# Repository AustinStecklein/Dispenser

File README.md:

# Dispenser
Creedmoor code base for the powder dispenser

# TODO List Software
- [ ] forward and back buttons dont function
- [ ] brightness/sound page sliders need to be prettier if possible
- [ ] calibrate, default settings, power off need yes and no image buttons
- [ ] Force the Subpages of Settings to not appear after clicking on the home button   and then clicking on Settings
- [ ] Keyboard does the same thing as the Settings subpages
- [ ] Replace the Boot Logo when the Program starts with a Creedmoor Logo

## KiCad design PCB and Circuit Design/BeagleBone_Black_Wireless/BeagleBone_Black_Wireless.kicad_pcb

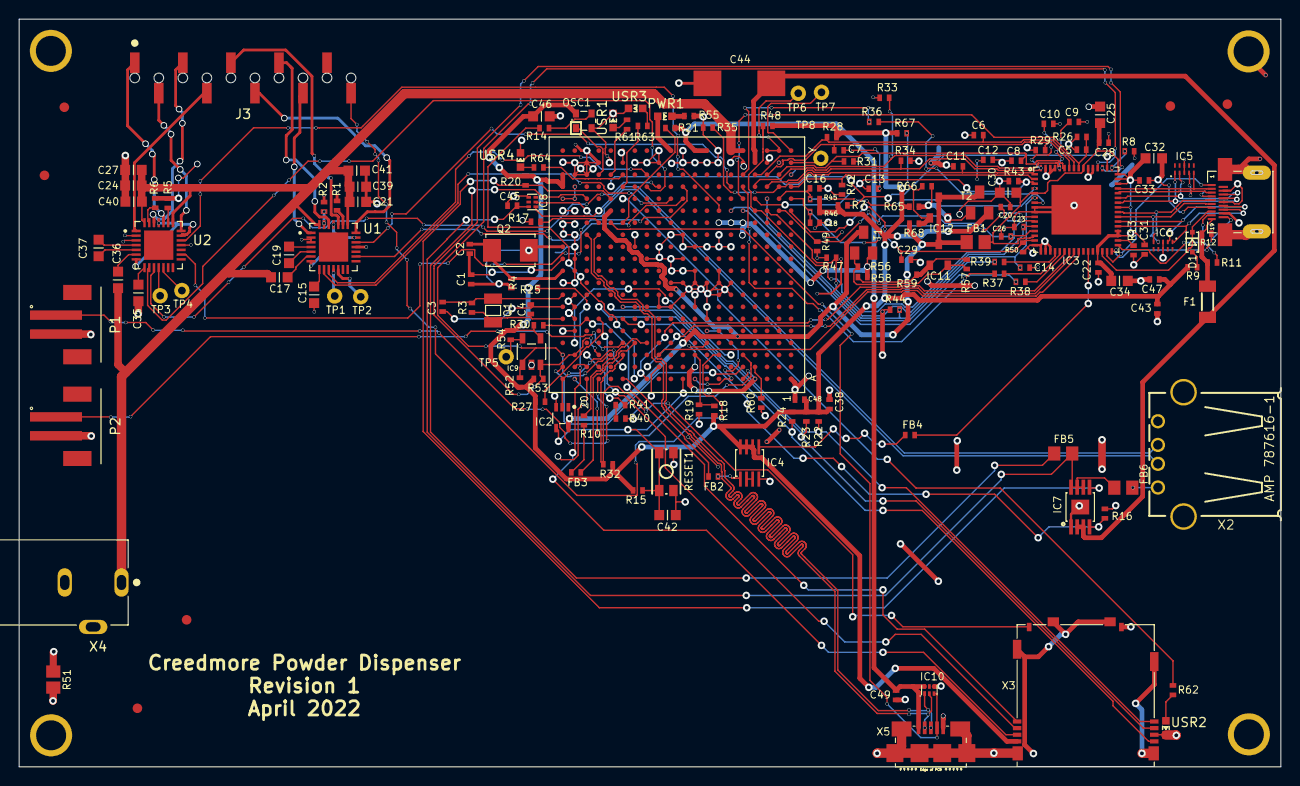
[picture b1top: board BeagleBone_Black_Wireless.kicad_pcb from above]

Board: 2 copper layers, 133.4 x 79.0 mm, 176 parts (0 on the bottom side), 159 nets.

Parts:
C1, C2, C3, C4: 18pF, 50V; C0402K
C5, C6, C7, C8, C9, C10, C11, C12, C13, C14, C16, C18, C20, C23, C26, C29: 47pF, 6.3V; C0402K
C15, C35: 10uF; C0603K
C17, C21, C24, C36, C39, C40: 100nF; C0603K
C19, C37: 22nF; C0603K
C22, C28, C31, C33, C38, C43, C45, C47, C48, C49: .1uF, 6.3V; C0402K
C25, C30, C32, C34, C42: 2.2uF, 6.3V; C0603K
C27, C41: 100uF; C0603K
C44: 220uF 6.3V; D_7343-31W
C46: 10uF,10V; C0603K
D1: RB751V40,115; SOD323(NXP)REFLOW
F1: 1206L025YR; SM-1206
FB1: 2.5k Ohm (BLM18BD252SN1D); 0805-RESISTOR
FB2, FB3, FB4: 1k BLM15AG102SN1D; R0402
FB5: 0.1 Ohm, 0805; 0805-RESISTOR
FB6: 150 Ohm 800mA; 0805-RESISTOR
FUD1, FUD2, FUD3, FUD4, FUD5, FUD6: FIDUCIAL; FIDUCIAL_40MIL
IC1: OSD3358
IC2: SN74LVC1G07DCK; SC70(TI-DCK)
IC3: TDA19988BHN/C1,557; SOT804-4(NXP)
IC4: SN74AUC1G74; SM8-8(TI)
IC5, IC6: IP4283CZ10-TBR; SOT1176-1(NXP)
IC7: TPS2051BDGN; MSOP-POWER.PAD-8(TI)
IC8, IC10: TPD4S012DRY; SON-6(TI)-DRY
IC9: 24LC32AT-I/OT; SOT23-5(MICROCHIP)
IC11: TLVH431 (SOT-23-3); DBZ_R-PDSO-G3
IC12: DNP TLVH431 (SOT-23-3); DBZ_R-PDSO-G3
J3: BG125-10-A-1-1-0440-N-D; GCT_BG125-10-A-1-1-0440-N-D
MGT1, MGT2, MGT3, MGT4: MOUNTING_HOLE
OSC1: ASDMB-24.576MHZ-LC-T; OSCILLATOR-2.5X2.0-BBB
P1, P2: B2B-PH-SM4-TB; JST_B2B-PH-SM4-TB
PWR1: LTST-C191TBKT; 0603-LED
Q1: 32.768kHz; CRYSTAL_3.2X1.5
Q2: 24 MHz; CRYSTAL_5X3.2MM
R1, R2, R5, R6: .11; R0402
R3: DNP 1M, 1%; R0402
R4: 1M, 1%; R0402
R7, R13, R15, R16, R22, R23, R24, R25, R27, R30, R32, R54, R60: 10k, 1%; R0402
R8, R10, R17, R20, R21, R37, R38, R39, R40, R41: 0, 1%; R0402
R9: 27k, 1%; R0402
R11, R12, R52, R53: 1.5k, 1%; R0402
R14: 33; R0402
R18, R19, R55: 4.75k, 1%; R0402
R26, R28, R29, R31, R33, R34, R35, R42, R43, R44, R45, R46, R47, R48, R49, R50: 100k, 1%; R0402
R36: 22; R0402
R51: .1, R0805; R0805
R56: 499; R0402
R57, R66: DNP; R0402
R58: 10k 1%; R0402
R59: 40.2k 1%; R0402
R61, R62, R63, R64: 1k; R0402
R65: DNP 499; R0402
R67: DNP 10k 1%; R0402
R68: DNP 40.2k 1%; R0402
RESET1: MINI_PUSHBUTTON
T1: MMBT2907; SOT23-BEC
T2: DNP MMBT2907; SOT23-BEC
TP1, TP2, TP3, TP4, TP5, TP6, TP7, TP8: TESTPAD_W_HOLE_1X1
U1, U2: TMC2208-LA-T; QFN50P500X500X90-29N
USR1, USR2, USR3, USR4: LTST-C191TBKT; 0603-LED
X1: 10118241-001RLF; HDMI-TYPE-D-10118241
X2: USB_HOST_W_CHASSIS_GND; USB_HOST_HORIZONTAL_W_CHASSIS_GND
X3: SCHA5B0200
X4: PJ-102B; CUI_PJ-102B
X5: 10118192-0001LF; 10118192-0001LF(MICRO-USB-B-AMPHENOL-FCI)

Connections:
/12MHZ: FB4.2, IC3.27
/12M_LOOP: IC4.2, IC4.3
/AIN1: IC1.C7, J3.10
/BAT_TEMP: IC1.W1, TP8.P$1
/BAT_VOLT: IC1.Y1, TP7.P$1
/CEC: D1.C, IC3.30, X1.15
/CLKOUT2: FB3.1, R10.1
/DVI_5V: F1.1, R11.1, R12.1, X1.19
/EHRPWM2A: IC1.U10, U2.16
/EHRPWM2B: IC1.T10, U1.16
/EXT_SWING: IC3.34, R13.1
/GPIO0_7: R40.1, R41.1
/GPIO0_26: IC1.T11, U1.9
/GPIO0_27: IC1.U12, U2.10
/GPIO1_14: IC1.V13, U1.10
/GPIO1_15: IC1.U13, U2.9
/GPIO3_21: IC1.A14, R14.2
/HDMICLK_DIS#: IC1.V17, OSC1.1
/HDMI_INT: IC1.U16, IC3.50, R7.2
/HPD: IC3.31, X1.1
/I2C0_SCL: IC1.C16, IC1.C20, IC3.52, IC9.1, R52.2
/I2C0_SDA: IC1.C17, IC1.C19, IC3.51, IC9.3, R53.2
/LCD.CLOCK: IC3.4, R36.1
/LCD.D0.B0--B3: C29.1, IC1.R1, IC3.15, R50.2
/LCD.D1.B1--B4: C26.1, IC1.R2, IC3.13, R49.2
/LCD.D2.B2--B5: C23.1, IC1.R3, IC3.12, R47.2
/LCD.D3.B3--B6: C20.1, IC1.R4, IC3.11, R48.1
/LCD.D4.B4--B7: C18.1, IC1.T1, IC3.10, R46.1
/LCD.D5.G0--G2: C16.1, IC1.T2, IC3.7, R45.1
/LCD.D6.G1--G3: C14.1, IC1.T3, IC3.6, R44.2
/LCD.D7.G2--G4: C13.1, IC1.T4, IC3.3, R43.2
/LCD.D8.G3--G5: C12.1, IC1.U1, IC3.2, R42.2
/LCD.D9.G4--G6: C11.1, IC1.U2, IC3.1, R35.2
/LCD.D10.G5--G7: C10.1, IC1.U3, IC3.64, R34.2
/LCD.D11.R0--R3: C9.1, IC1.U4, IC3.60, R33.2
/LCD.D12.R1--R4: C8.1, IC1.V2, IC3.59, R31.2
/LCD.D13.R2--R5: C7.1, IC1.V3, IC3.58, R29.2
/LCD.D14.R3--R6: C6.1, IC1.V4, IC3.57, R28.1
/LCD.D15.R4--R7: C5.1, IC1.T5, IC3.56, R26.2
/LCD.ENABLE: IC3.20, R39.1
/LCD.HSYNC: IC3.22, R38.1
/LCD.VSYNC: IC3.21, R37.1
/LDO_PGOOD: IC1.B5, IC1.B20
/M1A+: J3.1, U2.24
/M1A-: J3.2, U2.21
/M1B+: J3.3, U2.26
/M1B-: J3.4, U2.1
/M2A+: J3.5, U1.24
/M2A-: J3.6, U1.21
/M2B+: J3.7, U1.26
/M2B-: J3.8, U1.1
/MCU.LCD.CLK: IC1.V5, R36.2
/MCU.LCD.EN: IC1.R6, R39.2
/MCU.LCD.HS: IC1.R5, R38.2
/MCU.LCD.VS: IC1.U5, R37.2
/PMIC_INT: IC1.B18, IC1.B19
/PMIC_NWAKEUP: IC1.A19, IC1.C5
/PMIC_PGOOD: IC1.A20, IC1.B15, IC2.2
/SD.CD: IC1.C15, R32.1, X3.CD
/SD.CLK: IC1.G17, R24.1, X3.5
/SD.CMD: IC1.G18, R25.1, X3.3
/SD.D0: IC1.G16, R23.1, X3.7
/SD.D1: IC1.G15, R22.1, X3.8
/SD.D2: IC1.F18, R30.1, X3.1
/SD.D3: IC1.F17, R27.1, X3.2
/SPI1_CS0: IC1.C12, IC3.25
/SPI1_D0: IC1.B13, IC3.24
/SPI1_SCLK: IC1.A13, IC3.23
/SYS_RESET#: C42.1, IC1.A10, IC2.4, R15.2, RESET1.3, RESET1.4
/TEST: IC3.49, R8.2
/TIMER4: IC1.R7, U2.19
/TIMER6: IC1.U6, U1.19
/TX0+: IC3.40, IC6.5, X1.9
/TX0-: IC3.39, IC6.4, X1.11
/TX1+: IC3.43, IC5.2, X1.6
/TX1-: IC3.42, IC5.1, X1.8
/TX2+: IC3.45, IC5.5, X1.3
/TX2-: IC3.44, IC5.4, X1.5
/TXC+: IC3.38, IC6.2, X1.12
/TXC-: IC3.37, IC6.1, X1.14
/UART1_TXD: IC1.D15, P2.1
/UART2_RXD: IC1.A17, P1.1
/USB1_DRVVBUS: IC1.F15, IC7.4, R16.1
/USB1_OC#: IC1.T16, IC7.5, R20.2
/USB1_VBUS: FB5.2, IC1.T18
/USB.CLIENT.D+: IC1.N17, IC10.1, X5.D+
/USB.CLIENT.D-: IC1.N18, IC10.2, X5.D-
/USB.CLIENT.ID: IC1.P16, IC10.3, X5.ID
/USB.HOST.D+: IC1.R17, IC8.1, X2.3
/USB.HOST.D-: IC1.R18, IC8.2, X2.2
/USR0: IC1.V15, R64.2
/USR1: IC1.U15, R63.2
/USR2: IC1.T15, R62.2
/USR3: IC1.V16, R61.2
/VIN_BAT: IC1.Y2, IC1.Y3, TP6.P$1
/XDMA_EVENT_INTRO: FB2.2, IC4.1
AGND: IC1.A6, IC1.A9, IC1.E8
CGND: MGT1.P$1, MGT2.P$1, MGT3.P$1, MGT4.P$1, R51.2, X1.CG1, X1.CG2, X1.CG3, X1.CG4, X2.5, X2.6, X3.CGND1, X3.CGND2, X3.CGND3, X3.CGND4, X3.CGND5, X3.CGND6, X5.CGND1, X5.CGND2, X5.CGND3, X5.CGND4, X5.CGND5, X5.CGND6
GND: C5.2, C6.2, C7.2, C8.2, C9.2, C10.2, C11.2, C12.2, C13.2, C14.2, C15.1, C16.2, C18.2, C20.2, C21.1, C22.2, C23.2, C24.1, C25.2, C26.2, C27.1, C28.2, C29.2, C30.2, C31.2, C32.2, C33.2, C34.2, C35.1, C38.2, C39.1, C40.1, C41.1, C42.2, C43.2, C44.-, C45.2, C46.2, C47.2, C48.2, C49.2, IC1.A1, IC1.A18, IC1.E19, IC1.E20, IC1.F8, IC1.F19, IC1.G8, IC1.G9, IC1.G11, IC1.G12, IC1.G19, IC1.H6, IC1.H7, IC1.H8, IC1.H9, IC1.H10, IC1.H12, IC1.H19, IC1.J6, IC1.J7, IC1.J8, IC1.J9, IC1.J10, IC1.J11, IC1.J19, IC1.J20, IC1.K7, IC1.K9, IC1.K10, IC1.K11, IC1.K19, IC1.L10, IC1.L11, IC1.L12, IC1.L13, IC1.L19, IC1.M6, IC1.M7, IC1.M8, IC1.M9, IC1.M10, IC1.M12, IC1.M14, IC1.M19, IC1.N7, IC1.N10, IC1.N11, IC1.N14, IC1.N19, IC1.N20, IC1.P19, IC1.P20, IC1.R19, IC1.R20, IC1.T19, IC1.T20, IC1.U19, IC1.V1, IC1.V18, IC1.V19, IC1.W2, IC1.W3, IC1.W5, IC1.W6, IC1.W7, IC1.W8, IC1.W9, IC1.W10, IC1.W11, IC1.W12, IC1.W13, IC1.W14, IC1.W15, IC1.W16, IC1.W17, IC1.W18, IC1.W19, IC1.W20, IC1.Y7, IC1.Y10, IC1.Y12, IC1.Y15, IC1.Y18, IC2.3, IC3.8, IC3.9, IC3.16, IC3.17, IC3.18, IC3.19, IC3.53, IC3.54, IC3.61, IC3.62, IC3.63, IC3.65, IC4.4, IC5.3, IC5.8, IC6.3, IC6.8, IC7.1, IC7.9, IC8.4, IC9.2, IC10.4, OSC1.2, P1.2, P2.2, R1.2, R2.2, R5.2, R6.2, R8.1, R13.2, R16.2, R17.2, R19.2, R26.1, R29.1, R31.1, R33.1, R34.1, R35.1, R42.1, R43.1, R44.1, R47.1, R49.1, R50.1, R51.1, R55.1, R60.1, RESET1.1, RESET1.2, U1.2, U1.3, U1.18, U2.2, U2.3, U2.18, USR1.K, USR2.K, USR3.K, USR4.K, X1.4, X1.7, X1.10, X1.13, X1.16, X2.4, X3.6, X3.GND, X4.2, X5.GND
HDMI_1V8: C22.1, C25.1, C28.1, C30.1, C31.1, C32.1, C33.1, C34.1, FB1.2, IC3.5, IC3.14, IC3.29, IC3.35, IC3.36, IC3.41, IC3.46, IC3.47, IC3.48, IC3.55
unnamed: C1.1, IC1.M20, Q2.2, R4.2
unnamed: C1.2, C2.2, IC1.L20
unnamed: C2.1, IC1.K20, Q2.1, R4.1
unnamed: C3.1, IC1.H20, Q1.P$1, R3.2
unnamed: C3.2, C4.2, IC1.G20
unnamed: C4.1, IC1.F20, Q1.P$2, R3.1
unnamed: C15.2, U1.8
unnamed: C17.2, U1.6
unnamed: C19.1, U1.4
unnamed: C19.2, U1.5
unnamed: C35.2, U2.8
unnamed: C36.2, U2.6
unnamed: C37.1, U2.4
unnamed: C37.2, U2.5
unnamed: C45.1, FB5.1, FB6.1, IC7.6, IC7.7, IC7.8, IC8.6
unnamed: D1.A, R9.2
unnamed: FB2.1, IC1.A15
unnamed: FB3.2, IC1.D14
unnamed: FB4.1, IC4.5
unnamed: FB6.2, X2.1
unnamed: IC1.B4, R60.2
unnamed: IC1.B12, R40.2
unnamed: IC1.C6, IC1.D19
unnamed: IC1.C9, R18.2, R19.1
unnamed: IC1.C18, R41.2
unnamed: IC1.D13, R10.2
unnamed: IC1.P15, R21.1
unnamed: IC1.P17, R17.1
unnamed: IC3.32, R12.2, X1.18
unnamed: IC3.33, R11.2, X1.17
unnamed: IC9.5, R54.2, TP5.P$1
unnamed: IC11.1, R57.2, R58.2, R59.1
unnamed: IC11.2, R56.2, R57.1, T1.B
unnamed: IC12.1, R66.2, R67.2, R68.1
unnamed: IC12.2, R65.2, R66.1, T2.B
unnamed: OSC1.3, R14.1
unnamed: PWR1.K, R55.2
unnamed: R1.1, U1.23
unnamed: R2.1, U1.27
unnamed: R5.1, U2.23
unnamed: R6.1, U2.27
unnamed: R61.1, USR1.A
unnamed: R62.1, USR2.A
unnamed: R63.1, USR3.A
unnamed: R64.1, USR4.A
unnamed: TP1.P$1, U1.11
unnamed: TP2.P$1, U1.12
unnamed: TP3.P$1, U2.11
unnamed: TP4.P$1, U2.12
unnamed: U1.7, U1.20, U1.25
unnamed: U2.7, U2.20, U2.25
SYS_5V: C44.+, F1.2, IC1.W4, IC1.Y4, IC7.2, IC7.3
USB_DC: C49.1, IC1.Y8, IC1.Y9, IC10.6, R21.2, X5.VBUS
VDD_1V8: FB1.1, IC1.D10, IC1.E9, IC1.N16, IC1.R16, IC2.5, IC11.3, IC12.3, R59.2, R68.2, T1.C, T2.C
VDD_3V3A: IC1.N5, IC1.P5, IC1.P6, IC1.P7, R56.1, R58.1, T1.E
VDD_3V3AUX: IC1.Y11, PWR1.A
VDD_3V3B: C38.1, C43.1, C46.1, C47.1, C48.1, IC1.U20, IC1.V20, IC4.6, IC4.7, IC4.8, IC9.4, OSC1.4, R7.1, R9.1, R15.1, R18.1, R20.1, R22.2, R23.2, R24.2, R25.2, R27.2, R28.2, R30.2, R32.2, R45.2, R46.2, R48.2, R52.1, R53.1, R54.1, R65.1, R67.1, T2.E, X3.4
VDD_5V: C17.1, C21.2, C24.2, C27.2, C36.1, C39.2, C40.2, C41.2, IC1.Y5, IC1.Y6, U1.22, U1.28, U2.22, U2.28, X4.1
VDD_ADC: IC1.A4, IC1.A5, IC1.B9, IC1.D8

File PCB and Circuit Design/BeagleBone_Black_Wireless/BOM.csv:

Reference, Value,JLCPCB PN
C1,"18pF, 50V",
C10,"47pF, 6.3V",
C11,"47pF, 6.3V",C1567
C12,"47pF, 6.3V",
C13,"47pF, 6.3V",
C14,"47pF, 6.3V",
C15,10uF,
C16,"47pF, 6.3V",
C17,100nF,
C18,"47pF, 6.3V",
C19,22nF,
C2,"18pF, 50V",
C20,"47pF, 6.3V",
C21,100nF,
C22,".1uF, 6.3V",
C23,"47pF, 6.3V",
C24,100nF,
C25,"2.2uF, 6.3V",
C26,"47pF, 6.3V",
C27,100uF,
C28,".1uF, 6.3V",
C29,"47pF, 6.3V",
C3,"18pF, 50V",
C30,"2.2uF, 6.3V",
C31,".1uF, 6.3V",
C32,"2.2uF, 6.3V",
C33,".1uF, 6.3V",
C34,"2.2uF, 6.3V",
C35,10uF,
C36,100nF,
C37,22nF,
C38,".1uF, 6.3V",
C39,100nF,
C4,"18pF, 50V",
C40,100nF,
C41,100uF,
C42,"2.2uF, 6.3V",
C43,".1uF, 6.3V",
C44,220uF 6.3V,
C45,".1uF, 6.3V",
C46,"10uF,10V",
C47,".1uF, 6.3V",
C48,".1uF, 6.3V",
C49,".1uF, 6.3V",
C5,"47pF, 6.3V",
C6,"47pF, 6.3V",
C7,"47pF, 6.3V",
C8,"47pF, 6.3V",
C9,"47pF, 6.3V",
D1,"RB751V40,115",
F1,1206L025YR,
FB1,2.5k Ohm (BLM18BD252SN1D),
FB2,1k BLM15AG102SN1D,
FB3,1k BLM15AG102SN1D,
FB4,1k BLM15AG102SN1D,
FB5,"0.1 Ohm, 0805",
FB6,150 Ohm 800mA,
FUD1,FIDUCIAL,
FUD2,FIDUCIAL,
FUD3,FIDUCIAL,
FUD4,FIDUCIAL,
FUD5,FIDUCIAL,
FUD6,FIDUCIAL,
IC1,OSD3358,
IC10,TPD4S012DRY,
IC11,TLVH431 (SOT-23-3),
IC12,DNP TLVH431 (SOT-23-3),
IC2,SN74LVC1G07DCK,
IC3,"TDA19988BHN/C1,557",
IC4,SN74AUC1G74,
IC5,IP4283CZ10-TBR,
IC6,IP4283CZ10-TBR,
IC7,TPS2051BDGN,
IC8,TPD4S012DRY,
IC9,24LC32AT-I/OT,
J3,BG125-10-A-1-1-0440-N-D,
MGT1,MOUNTING_HOLE,
MGT2,MOUNTING_HOLE,
MGT3,MOUNTING_HOLE,
MGT4,MOUNTING_HOLE,
OSC1,ASDMB-24.576MHZ-LC-T,
P1,B2B-PH-SM4-TB,
P2,B2B-PH-SM4-TB,
PWR1,LTST-C191TBKT,
Q1,32.768kHz,
Q2,24 MHz,
R1,0.11,
R10,"0, 1%",
R11,"1.5k, 1%",
R12,"1.5k, 1%",
R13,"10k, 1%",
R14,33,
R15,"10k, 1%",
R16,"10k, 1%",
R17,"0, 1%",
R18,"4.75k, 1%",
R19,"4.75k, 1%",
R2,0.11,
R20,"0, 1%",
R21,"0, 1%",
R22,"10k, 1%",
R23,"10k, 1%",
R24,"10k, 1%",
R25,"10k, 1%",
R26,"100k, 1%",
R27,"10k, 1%",
R28,"100k, 1%",
R29,"100k, 1%",
R3,"DNP 1M, 1%",
R30,"10k, 1%",
R31,"100k, 1%",
R32,"10k, 1%",
R33,"100k, 1%",
R34,"100k, 1%",
R35,"100k, 1%",C25086
R36,22,
R37,"0, 1%",
R38,"0, 1%",
R39,"0, 1%",
R4,"1M, 1%",
R40,"0, 1%",
R41,"0, 1%",
R42,"100k, 1%",
R43,"100k, 1%",
R44,"100k, 1%",
R45,"100k, 1%",
R46,"100k, 1%",
R47,"100k, 1%",
R48,"100k, 1%",
R49,"100k, 1%",
R5,0.11,
R50,"100k, 1%",
R51,".1, R0805",
R52,"1.5k, 1%",
R53,"1.5k, 1%",
R54,"10k, 1%",
R55,"4.75k, 1%",
R56,499,
R57,DNP,
R58,10k 1%,
R59,40.2k 1%,
R6,0.11,
R60,"10k, 1%",
R61,1k,
R62,1k,
R63,1k,
R64,1k,
R65,DNP 499,
R66,DNP,
R67,DNP 10k 1%,
R68,DNP 40.2k 1%,
R7,"10k, 1%",
R8,"0, 1%",
R9,"27k, 1%",
RESET1,MINI_PUSHBUTTON,
T1,MMBT2907,
T2,DNP MMBT2907,
TP1,TESTPAD_W_HOLE_1X1,
TP2,TESTPAD_W_HOLE_1X1,
TP3,TESTPAD_W_HOLE_1X1,
TP4,TESTPAD_W_HOLE_1X1,
TP5,TESTPAD_W_HOLE_1X1,
TP6,TESTPAD_W_HOLE_1X1,
TP7,TESTPAD_W_HOLE_1X1,
TP8,TESTPAD_W_HOLE_1X1,
U1,TMC2208-LA-T,
U2,TMC2208-LA-T,
USR1,LTST-C191TBKT,
USR2,LTST-C191TBKT,
USR3,LTST-C191TBKT,
USR4,LTST-C191TBKT,
X1,10118241-001RLF,
X2,USB_HOST_W_CHASSIS_GND,
X3,SCHA5B0200,
X4,PJ-102B,
X5,10118192-0001LF,

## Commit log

2022-01-15 Basic file structure
2022-01-15 updated the TODO files
2022-01-15 updated the todos
2022-01-15 updated structure and readme to follow
2022-01-15 updated for check boxes
2022-01-16 basic threading framework
2022-01-19 Add files via upload
    Beginning code for frontend
2022-01-19 fixed event handler and threading
2022-01-19 added framework for driver classes
2022-01-19 tested
2022-01-20 Screenshots of Mockup
2022-01-24 num pad testing
2022-01-24 worked
2022-01-24 Current Root file for Front End
2022-01-24 numpad
2022-01-24 made a folder
2022-02-08 added jonathans code but its out of date
2022-02-09 tried out some other ways of using tkinter
2022-02-09 pycache
2022-02-09 reorg
2022-02-09 Test
2022-02-10 stuff
2022-02-14 Stuffs
2022-02-14 home
2022-02-14 backend framework
2022-02-14 Update StepperDrivers.py
    added empty functions to run GUI test
2022-02-15 pycharm
2022-02-16 started over T_T
2022-02-16 Things
2022-02-16 images
2022-02-16 arrows
2022-02-16 git ignore added
2022-02-16 got page switching to work :D
2022-02-18 Meeting Notes
2022-02-22 started save and settings pages
2022-02-22 Images Solution Solved
2022-02-23 Pics
2022-02-25 SAve Page
2022-02-28 did some settings pages
    description
2022-02-28 pycache probs
2022-03-02 settings pages
2022-03-06 load and view pages
2022-03-07 cache
2022-03-07 Updated Pics and KEyboard
2022-03-10 Updated Keyboard
2022-03-16 calibrate dialogue
2022-03-16 nice
2022-03-18 Keyboard almost fixed
2022-03-20 Merged code bases
2022-03-21 Merged!!!!!!!!!!!!
2022-03-22 Miked
2022-03-23 settings now work
2022-03-25 Comments
2022-03-28 UI fixes
    comments
    font fixes
    removed redundant functions in backend
2022-03-28 some todo comments
2022-03-28 Full screen
2022-03-28 Create temp
2022-03-28 adding backend to code
2022-03-28 started backend
2022-03-28 new ui test folder
2022-03-29 Fonts and other things
2022-03-30 Comments Update
2022-03-30 found a guide to fix feed buttons
2022-03-30 Comments on Comments
2022-03-30 merged
2022-03-30 stop buttons
2022-03-30 HTML DOC
2022-03-30 numpad is work
2022-03-30 tidy
2022-03-30 auto dispense
2022-03-30 Weekly Reportd
2022-03-31 Added Close on Unit Popup and other things
2022-03-31 Checklist
2022-03-31 Finances Stuff
2022-04-01 Arrow Buttons on Load and View
2022-04-01 Updated MAIN
2022-04-01 backend linking
2022-04-01 added database with save button
2022-04-01 fixed values
2022-04-01 fixed card insert function
2022-04-01 fixex
2022-04-01 added quotes around values
2022-04-02 Added docs
2022-04-03 edrtsh
2022-04-03 Screen shots
2022-04-04 added BOM
2022-04-04 added budget
2022-04-04 updated checklist
2022-04-04 dale
2022-04-04 lkjlk
2022-04-04 file moving
2022-04-04 exec sum
2022-04-05 What a handsome man that summary describes
2022-04-06 sdfg
2022-04-06 Wham
